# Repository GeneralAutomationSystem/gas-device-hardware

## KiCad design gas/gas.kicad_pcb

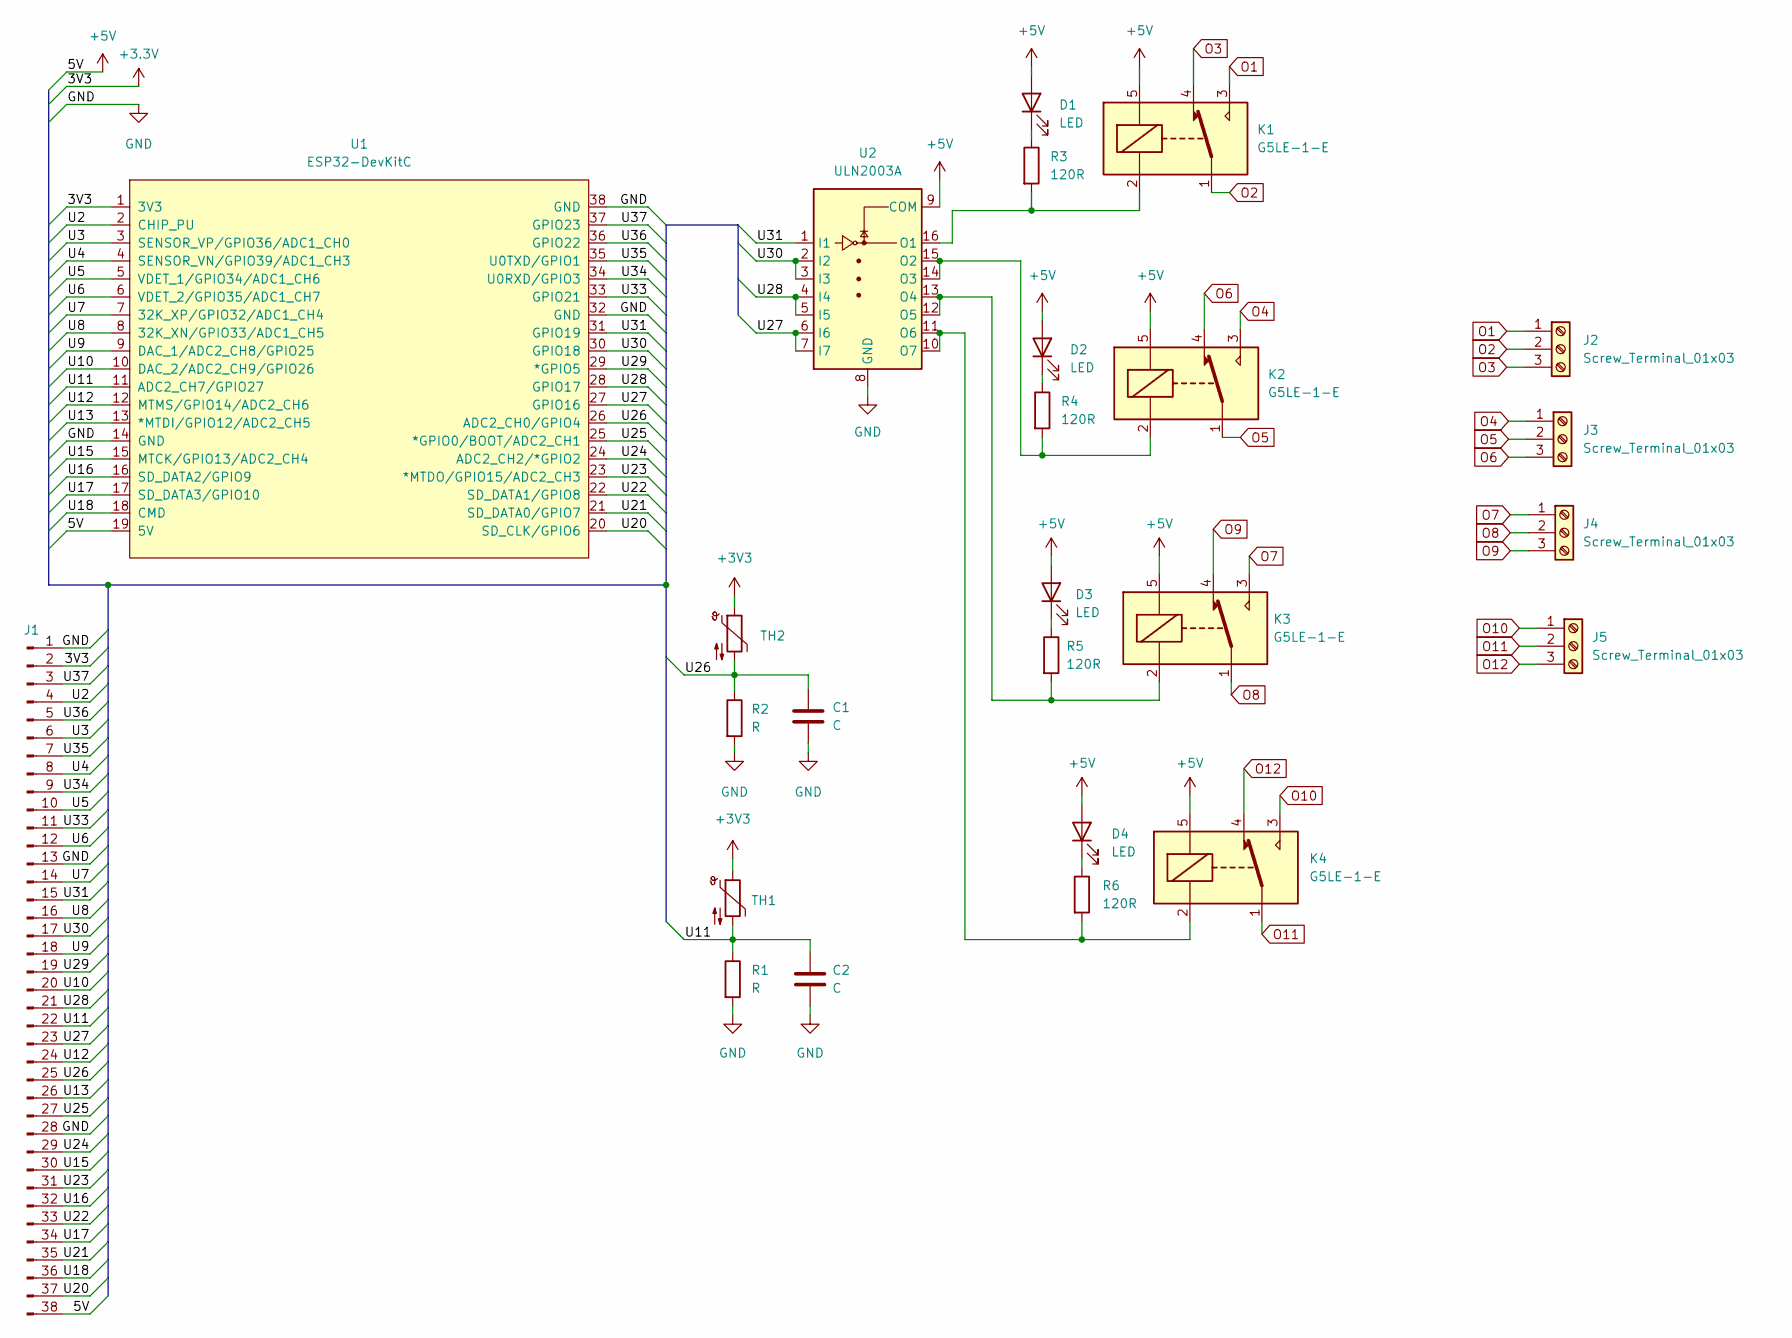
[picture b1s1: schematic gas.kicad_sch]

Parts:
C1, C2: C; C_0603_1608Metric
D1, D2, D3, D4: LED; LED_0603_1608Metric
J1: Conn_01x38_Male; PinHeader_2x19_P2.54mm_Vertical
J2, J3, J4, J5: Screw_Terminal_01x03; TerminalBlock_Phoenix_MKDS-1,5-3-5.08_1x03_P5.08mm_Horizont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
K1, K2, K3, K4: G5LE-1-E; Relay_SPDT_Omron-G5LE-1
R1, R2: R; C_0603_1608Metric
R3, R4, R5, R6: 120R; R_0603_1608Metric
TH1, TH2: Thermistor_NTC; R_0603_1608Metric
U1: ESP32-DevKitC
U2: ULN2003A; SOIC-16_3.9x9.9mm_P1.27mm

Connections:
+5V: D1.2 (A), D2.2 (A), D3.2 (A), D4.2 (A), J1.38, K1.5, K2.5, K3.5, K4.5, U1.19 (5V), U2.9 (COM)
/U2: J1.4, U1.2 (CHIP_PU)
/U3: J1.6, U1.3 (SENSOR_VP/GPIO36/ADC1_CH0)
/U4: J1.8, U1.4 (SENSOR_VN/GPIO39/ADC1_CH3)
/U5: J1.10, U1.5 (VDET_1/GPIO34/ADC1_CH6)
/U6: J1.12, U1.6 (VDET_2/GPIO35/ADC1_CH7)
/U7: J1.14, U1.7 (32K_XP/GPIO32/ADC1_CH4)
/U8: J1.16, U1.8 (32K_XN/GPIO33/ADC1_CH5)
/U9: J1.18, U1.9 (DAC_1/ADC2_CH8/GPIO25)
/U10: J1.20, U1.10 (DAC_2/ADC2_CH9/GPIO26)
/U11: C2.1, J1.22, R1.1, TH1.2, U1.11 (ADC2_CH7/GPIO27)
/U12: J1.24, U1.12 (MTMS/GPIO14/ADC2_CH6)
/U13: J1.26, U1.13 (*MTDI/GPIO12/ADC2_CH5)
/U15: J1.30, U1.15 (MTCK/GPIO13/ADC2_CH4)
/U16: J1.32, U1.16 (SD_DATA2/GPIO9)
/U17: J1.34, U1.17 (SD_DATA3/GPIO10)
/U18: J1.36, U1.18 (CMD)
/U20: J1.37, U1.20 (SD_CLK/GPIO6)
/U21: J1.35, U1.21 (SD_DATA0/GPIO7)
/U22: J1.33, U1.22 (SD_DATA1/GPIO8)
/U23: J1.31, U1.23 (*MTDO/GPIO15/ADC2_CH3)
/U24: J1.29, U1.24 (ADC2_CH2/*GPIO2)
/U25: J1.27, U1.25 (*GPIO0/BOOT/ADC2_CH1)
/U26: C1.1, J1.25, R2.1, TH2.2, U1.26 (ADC2_CH0/GPIO4)
/U27: J1.23, U1.27 (GPIO16), U2.6 (I6), U2.7 (I7)
/U28: J1.21, U1.28 (GPIO17), U2.4 (I4), U2.5 (I5)
/U29: J1.19, U1.29 (*GPIO5)
/U30: J1.17, U1.30 (GPIO18), U2.2 (I2), U2.3 (I3)
/U31: J1.15, U1.31 (GPIO19), U2.1 (I1)
/U33: J1.11, U1.33 (GPIO21)
/U34: J1.9, U1.34 (U0RXD/GPIO3)
/U35: J1.7, U1.35 (U0TXD/GPIO1)
/U36: J1.5, U1.36 (GPIO22)
/U37: J1.3, U1.37 (GPIO23)
GND: C1.2, C2.2, J1.1, J1.13, J1.28, R1.2, R2.2, U1.14 (GND), U1.32 (GND), U1.38 (GND), U2.8 (GND)
unnamed: D1.1 (K), R3.1
unnamed: D2.1 (K), R4.1
unnamed: D3.1 (K), R5.1
unnamed: D4.1 (K), R6.1
unnamed: K1.2, R3.2, U2.16 (O1)
unnamed: K2.2, R4.2, U2.14 (O3), U2.15 (O2)
unnamed: K3.2, R5.2, U2.12 (O5), U2.13 (O4)
unnamed: K4.2, R6.2, U2.10 (O7), U2.11 (O6)
O1: J2.1, K1.3
O2: J2.2, K1.1
O3: J2.3, K1.4
O4: J3.1, K2.3
O5: J3.2, K2.1
O6: J3.3, K2.4
O7: J4.1, K3.3
O8: J4.2, K3.1
O9: J4.3, K3.4
O10: J5.1, K4.3
O11: J5.2, K4.1
O12: J5.3, K4.4

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
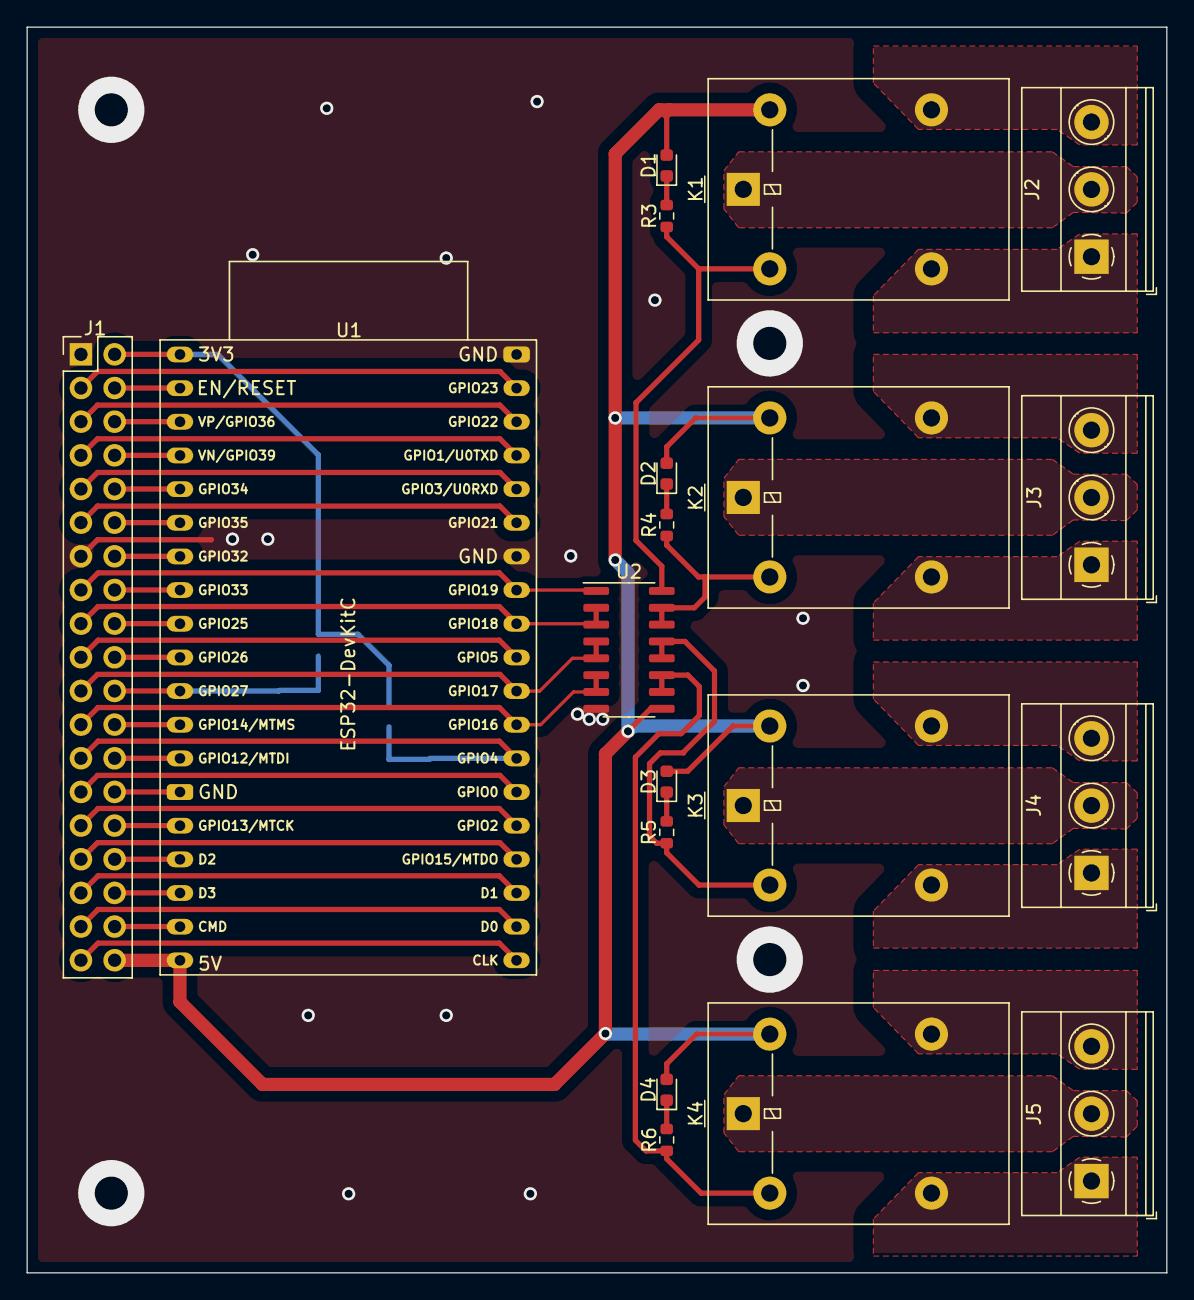
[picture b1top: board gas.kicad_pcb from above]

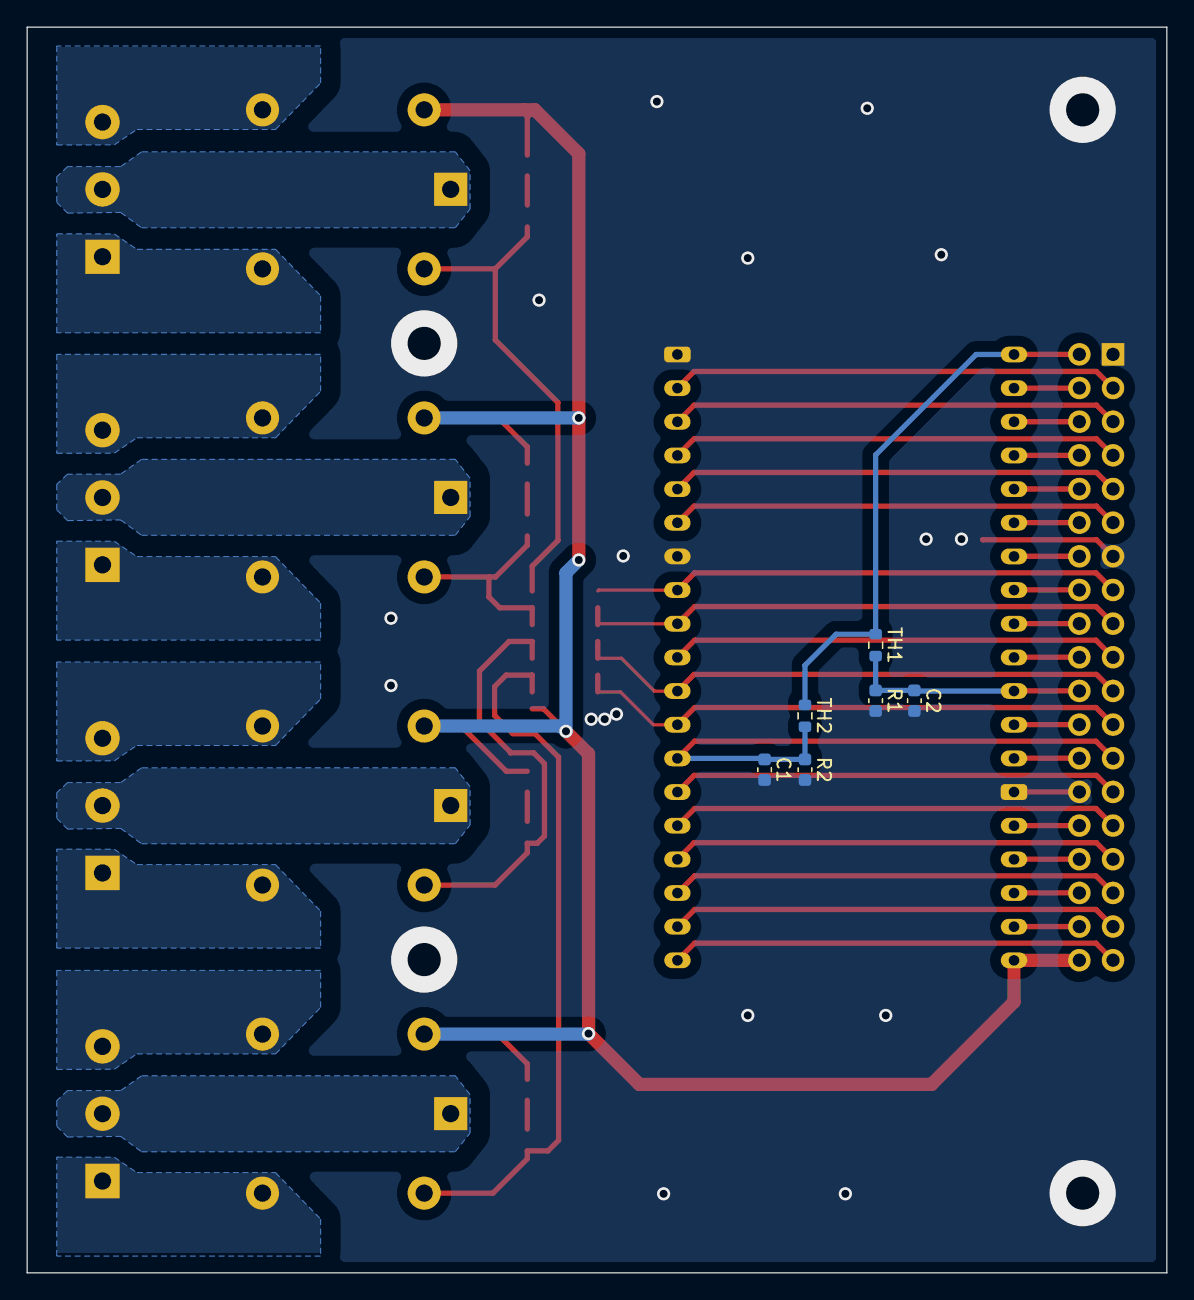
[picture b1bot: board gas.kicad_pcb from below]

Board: 2 copper layers, 86.0 x 94.0 mm, 25 parts (6 on the bottom side), 56 nets.

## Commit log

2022-03-15 feat: init
2022-03-17 basic schema and pcb
2022-04-06 feat: pcb update, box init
2022-05-18 feat: update to final
